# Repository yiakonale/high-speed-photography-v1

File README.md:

# High Speed Photography Unit V1

The problem with capturing high-speed photos boils down to how fast the camera can sample the subject. In nearly all cameras digital or analog, it comes down to the shutter speed. The shutter speed dictates how long the sensor (analog or digital) is exposed for, and therefore the "speed" of the photo. Regular digital cameras can expose a photo to 1/250 or 1/500 of a second. The fastest camera I own is an SLR with a mechanical shutter that can do 1/4000 of a second, which means that the film is exposed for 250us. One can optimize for faster and faster shutter speeds but the next bottleneck becomes the sensor itself. The less time you expose for, the less light the sensor can absorb. You can optimize for maximum light sensitivity but that's when the cost also skyrockets.

One workaround to this, is instead of relying on an ultra-fast shutter for quick exposure, instead using an ultra-fast light source to expose the event. The camera is set up to take a long exposure with large aperture and in complete darkness. When the event is you wish to capture takes place, the light source is triggered and exposes the scene for a very short instant. This works in the reverse way as before, as we now control the light source and leave the shutter wide open. The advantage to doing this is that you can use any regular camera, so long as you can take a long exposure. In order to know when you should pulse the light source, you need a way of knowing when your event is taking place, and very quickly triggerring a flash of light. A good video explanation of this concept can be found [here](https://www.youtube.com/watch?v=P-4pbFcERnk).

A reliable way of quickly detecting when to trigger the light source is to use acoustic waves or sound. The only downside to this is that the event itself has to produce some kind of noise or sound at the instant we wish to capture. Fortunately, there are many such events that produce a noise such as a balloon pop, champagne popping, things smashing into other objects, etc.
To capture a clean photo an event, we need to produce a pulse of light to expose the scene. The difficulty is creating a flash which is both bright enough and short enough to not cause blurring. Fortunately modern camera flashes are more than capable of producing sharp, bright flashes in an instant. Such flashtubes commonly contain high-pressure xenon gas in a sealed glass tube that get ionized by a pulse of high-voltage, momentarily allowing a large amount of current to flow through the tube which creates the bright flash. The gas can be ionized by wrapping a coil of wire around the glass tube and pulsing high-voltage. The high-voltage can capacitively couple through the gas and create plasma. The ends of the flashtube are also connected to a high voltage DC source, usually a capacitor. When the plasma is initially created, the strong electric field inside the tube accelerates the charged particles, creating a cascading avalanche effect until all or most of the gas is ionized. Once a low impedance connection is established through the plasma, the capacitor can rapidly discharge through the glass, heating it in the process and creating a bright flash of light.

###### Source: https://www.ecplaza.net/products/xenon-flash-lamp_3895024

To make this work, we need 3 main components. The first is a sound detector that can sense changes in air pressure that will generate the signal for the light to flash. We want this to be sensitive enough to detect sounds from a few meters distance, but not too sensitive to avoid accidental misfires. Something adjustable would be ideal. The second is a trigger circuit that can ionize the flashtube when the signal is sent by the detector. A trigger transformer in combination with an electronic switch is often used to create the HV pulse. I salvaged the trigger transformer, high-voltage capacitor as well as the flashtube from an old digital camera, though I've also seen them being used in wall mounted fire alarm sirens like [this one](https://www.shutterstock.com/video/clip-10242920-fire-alarm-emergency-flashing-light) as these use a similar circuit. You can actually just make out the coil of wire around the flashlamp in the center. You can also buy the entire circuit on [Ebay](https://www.ebay.ca/itm/125804677365). Lastly, we'll need a step-up converter to charge our capacitor, usually in the range of 300-400V and a few tens of microfarads.

###### (Left) Digital camera opened with high-voltage module and flashlamp visible in the middle (Right) Holding the high-voltage module from its HV capacitor. Trigger transformer visible in the middle of the PCB (orange). Flashtube visible just behind with its 3 wires: +, -, HV trigger.

I decided to design 3 PCBs, one for each subcircuit and then connect them together somehow. Not a lot of thought went into this phase as will be evident later on. The trigger circuit is really simple. It consists of an electronic switch, in this case a thyristor that can safely control the high-voltage pulse. I've also seen this being done with IGBTs but thyristors are easier to find for this application. To create the high voltage pulse, we need a high turn-ratio transformer, as well as a series capacitor. This small capacitor slowly charges through a resistor and rapidly discharges through the primary of the transformer, creating a high voltage spark on the output, similar to an electrostatic discharge. This is enough to break down the gas inside the tube.

TODO:
- trigger cct construction
- boost cct construction
- tuning capacitance

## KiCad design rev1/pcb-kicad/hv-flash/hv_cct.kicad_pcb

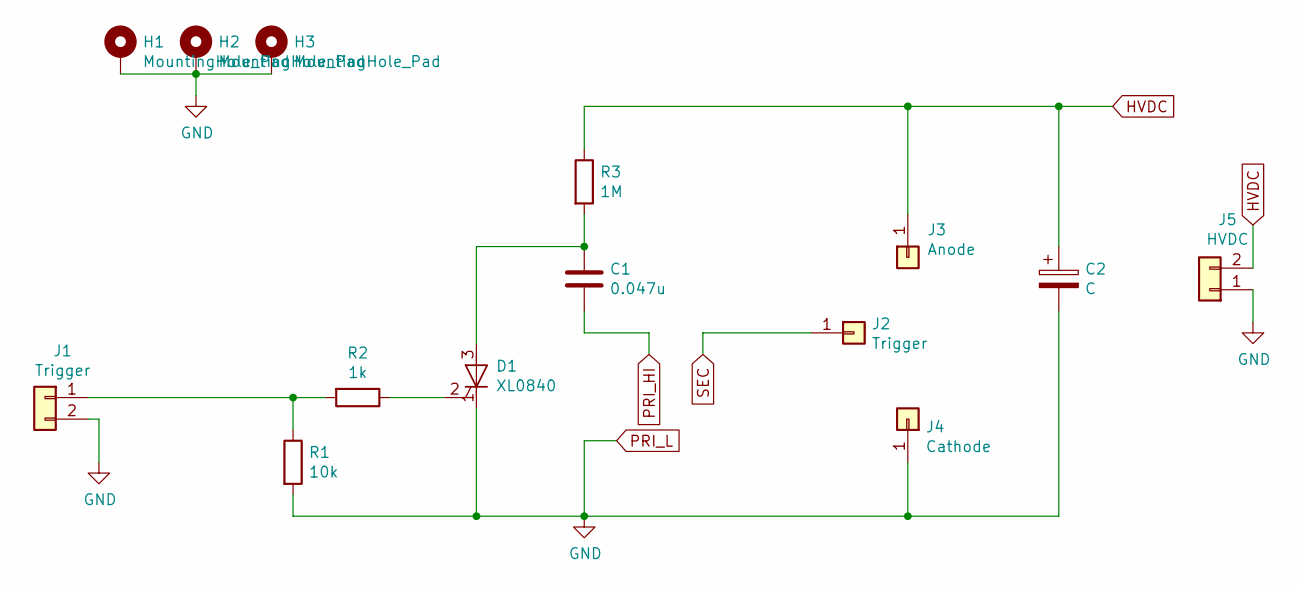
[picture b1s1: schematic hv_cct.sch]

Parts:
C1: 0.047u; C_Rect_L10.3mm_W5.0mm_P7.50mm_MKS4
C2: C; CP_Radial_D7.5mm_P2.50mm
D1: XL0840; TO-92_Inline_Wide
H1, H2, H3: MountingHole_Pad; MountingHole_3.2mm_M3_Pad
J1: Trigger; PinHeader_1x02_P2.54mm_Vertical
J2: Trigger; PinHeader_1x01_P2.54mm_Vertical
J3: Anode; PinHeader_1x01_P2.54mm_Vertical
J4: Cathode; PinHeader_1x01_P2.54mm_Vertical
J5: HVDC; PinHeader_1x02_P2.54mm_Vertical
R1: 10k; R_Axial_DIN0207_L6.3mm_D2.5mm_P7.62mm_Horizontal
R2: 1k; R_Axial_DIN0207_L6.3mm_D2.5mm_P7.62mm_Horizontal
R3: 1M; R_Axial_DIN0207_L6.3mm_D2.5mm_P7.62mm_Horizontal

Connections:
HVDC: C2.1, J3.1, J5.2, R3.1
unnamed: C1.1, D1.3 (A), R3.2
unnamed: D1.2 (G), R2.1
unnamed: J1.1, R1.1, R2.2
PRI_HI: C1.2
PRI_L: C2.2, D1.1 (K), H1.1, H2.1, H3.1, J1.2, J4.1, J5.1, R1.2
SEC: J2.1

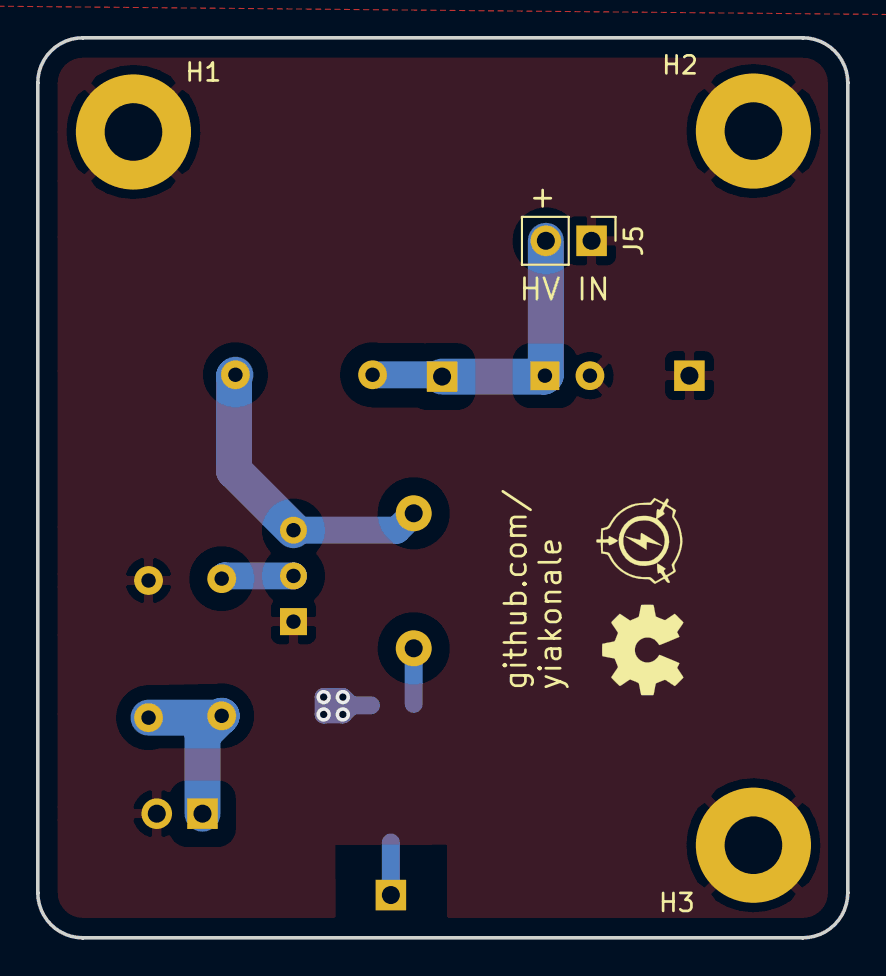
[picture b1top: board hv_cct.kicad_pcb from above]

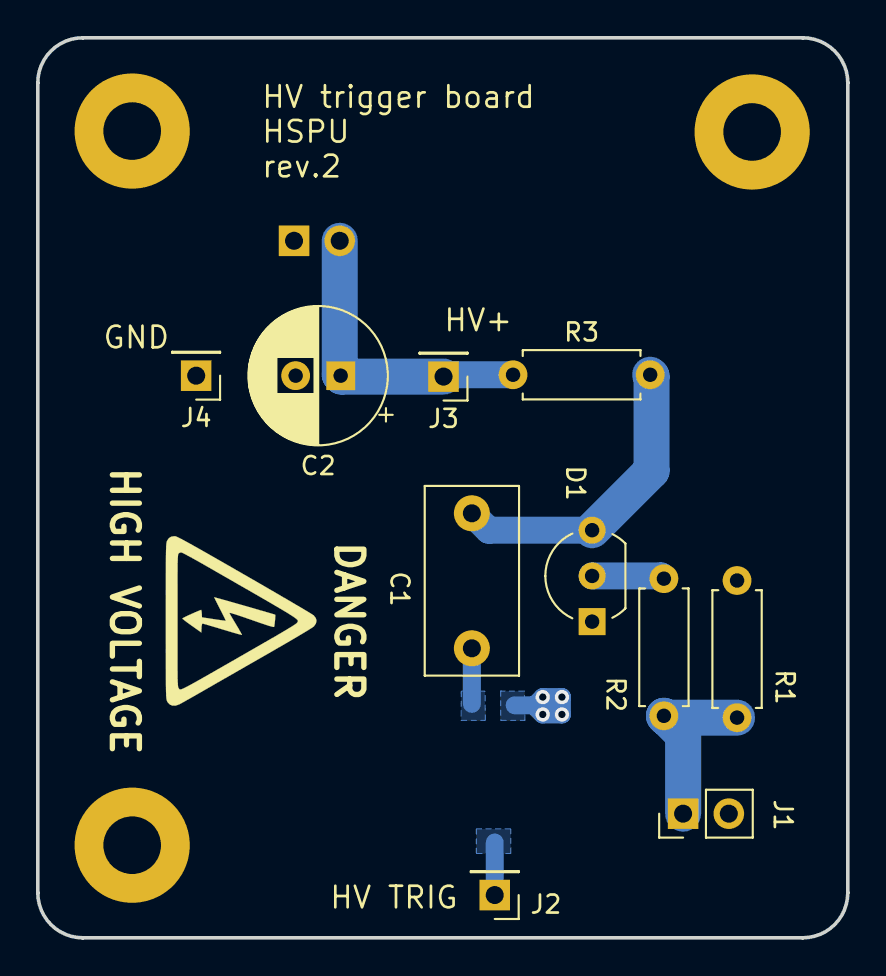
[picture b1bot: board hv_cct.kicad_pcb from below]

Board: 2 copper layers, 45.0 x 50.0 mm, 14 parts (10 on the bottom side), 5 nets.

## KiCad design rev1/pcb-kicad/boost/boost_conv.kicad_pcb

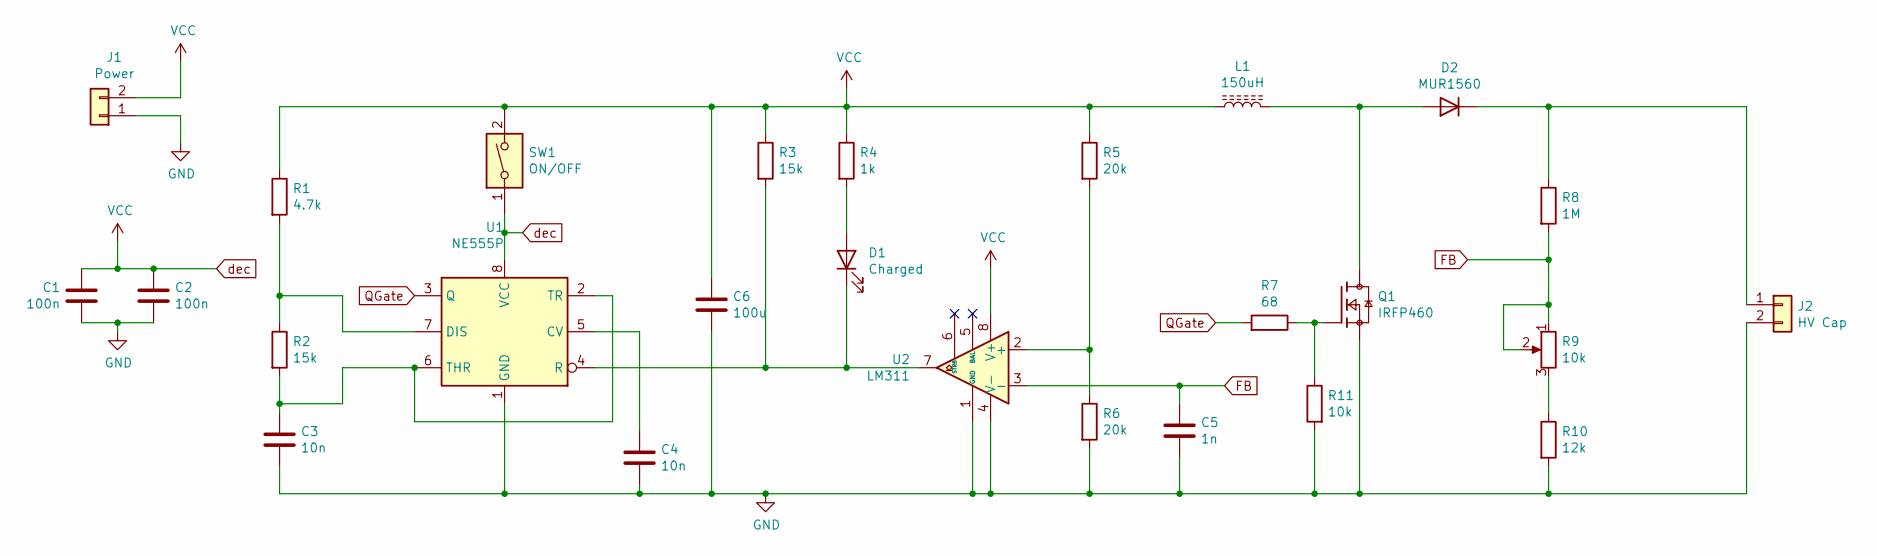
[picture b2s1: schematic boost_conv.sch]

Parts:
C1, C2: 100n; C_Disc_D5.0mm_W2.5mm_P5.00mm
C3, C4: 10n; C_Disc_D5.0mm_W2.5mm_P5.00mm
C5: 1n; C_Disc_D5.0mm_W2.5mm_P5.00mm
C6: 100u; CP_Radial_D8.0mm_P2.50mm
D1: Charged; LED_D5.0mm
D2: MUR1560; TO-220-2_Vertical
J1: Power; PinHeader_1x02_P2.54mm_Vertical
J2: HV Cap; PinHeader_1x02_P2.54mm_Vertical
L1: 150uH; L_Toroid_Vertical_L26.7mm_W14.0mm_P10.16mm_Pulse_D
Q1: IRFP460; TO-247-3_Vertical; PARTREV A
R1: 4.7k; R_Axial_DIN0207_L6.3mm_D2.5mm_P7.62mm_Horizontal
R2, R3: 15k; R_Axial_DIN0207_L6.3mm_D2.5mm_P7.62mm_Horizontal
R4: 1k; R_Axial_DIN0207_L6.3mm_D2.5mm_P7.62mm_Horizontal
R5, R6: 20k; R_Axial_DIN0207_L6.3mm_D2.5mm_P7.62mm_Horizontal
R7: 68; R_Axial_DIN0207_L6.3mm_D2.5mm_P7.62mm_Horizontal
R8: 1M; R_Axial_DIN0207_L6.3mm_D2.5mm_P7.62mm_Horizontal
R9: 10k; Potentiometer_Bourns_3296W_Vertical
R10: 12k; R_Axial_DIN0207_L6.3mm_D2.5mm_P7.62mm_Horizontal
R11: 10k; R_Axial_DIN0207_L6.3mm_D2.5mm_P7.62mm_Horizontal
SW1: ON/OFF; PinHeader_1x02_P2.54mm_Vertical
U1: NE555P; DIP-8_W7.62mm
U2: LM311; DIP-8_W7.62mm

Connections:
FB: C5.1, R8.2, R9.1, R9.2, U2.3 (-)
GND: C1.2, C2.2, C3.2, C4.2, C5.2, C6.2, J1.1, J2.2, Q1.3, R6.2, R10.2, R11.2, U1.1 (GND), U2.1 (GND), U2.4 (V-)
unnamed: C3.1, R2.2, U1.2 (TR), U1.6 (THR)
unnamed: C4.1, U1.5 (CV)
unnamed: D1.1 (K), R3.2, U1.4 (R), U2.7
unnamed: D1.2 (A), R4.2
unnamed: D2.1 (K), J2.1, R8.1
unnamed: D2.2 (A), L1.1, Q1.2
unnamed: Q1.1, R7.1, R11.1
unnamed: R1.2, R2.1, U1.7 (DIS)
unnamed: R5.2, R6.1, U2.2 (+)
unnamed: R9.3, R10.1
QGate: R7.2, U1.3 (Q)
dec: C1.1, C2.1, C6.1, J1.2, L1.2, R1.1, R3.1, R4.1, R5.1, SW1.1, SW1.2, U1.8 (VCC), U2.8 (V+)

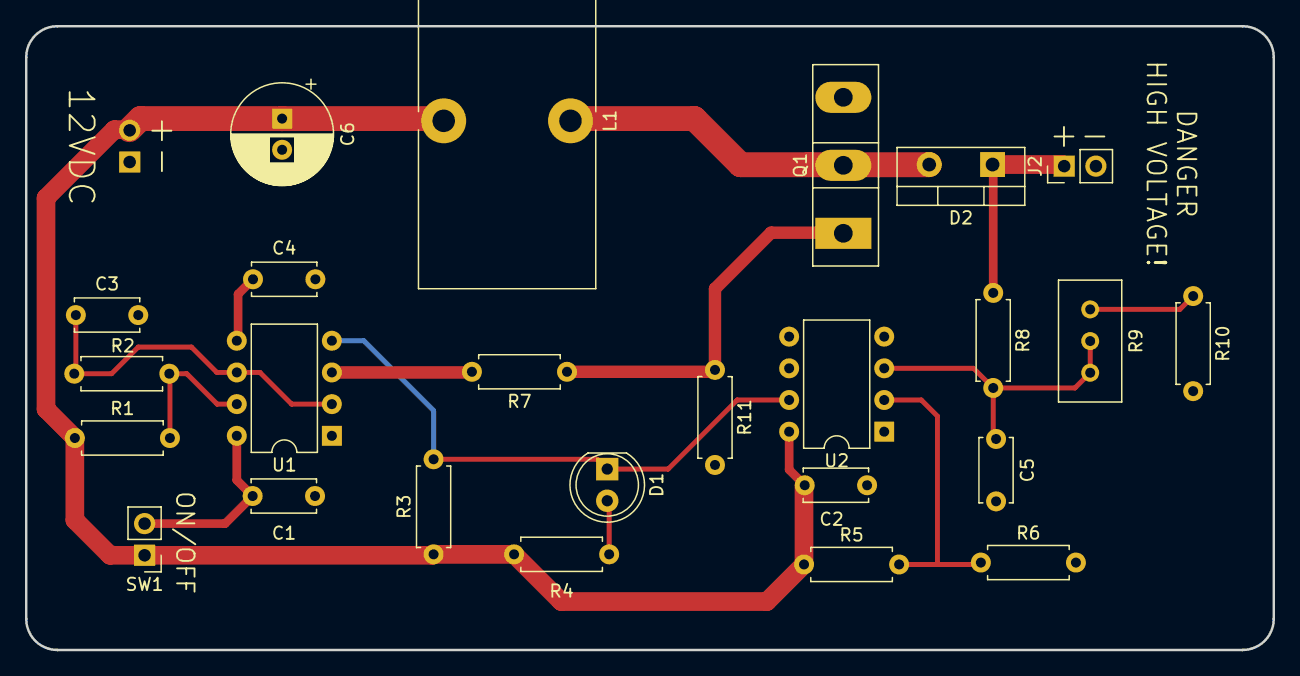
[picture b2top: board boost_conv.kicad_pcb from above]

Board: 2 copper layers, 100.0 x 50.0 mm, 26 parts (1 on the bottom side), 14 nets.

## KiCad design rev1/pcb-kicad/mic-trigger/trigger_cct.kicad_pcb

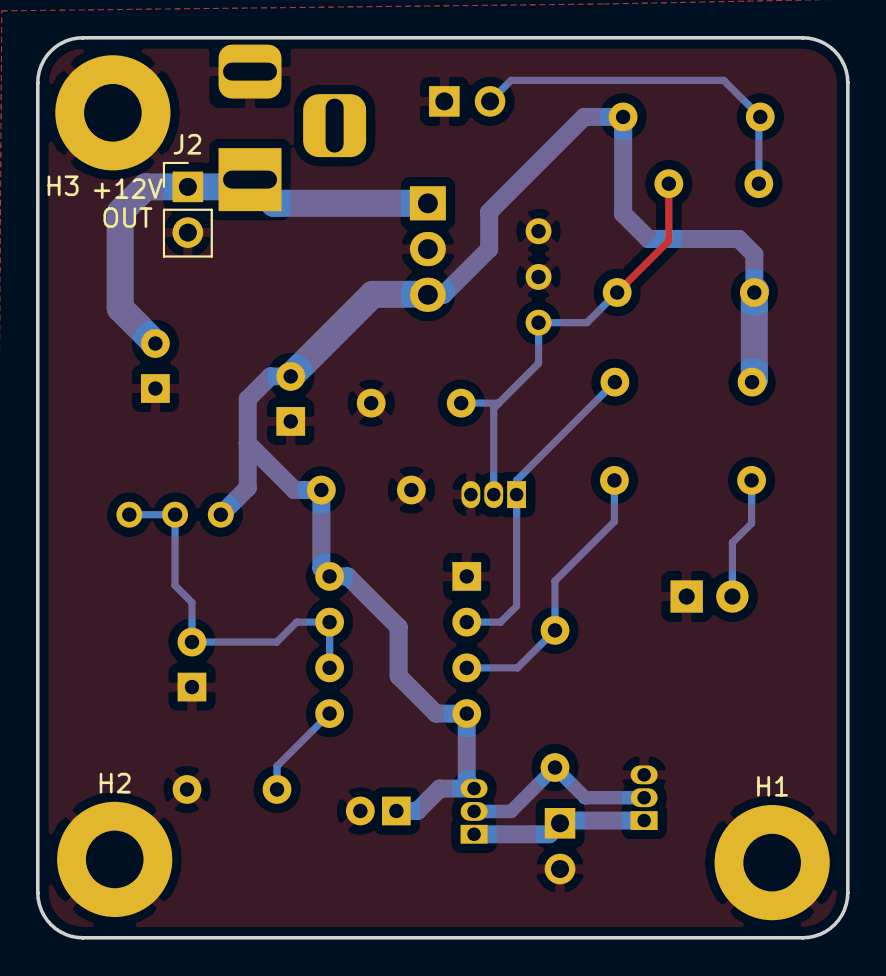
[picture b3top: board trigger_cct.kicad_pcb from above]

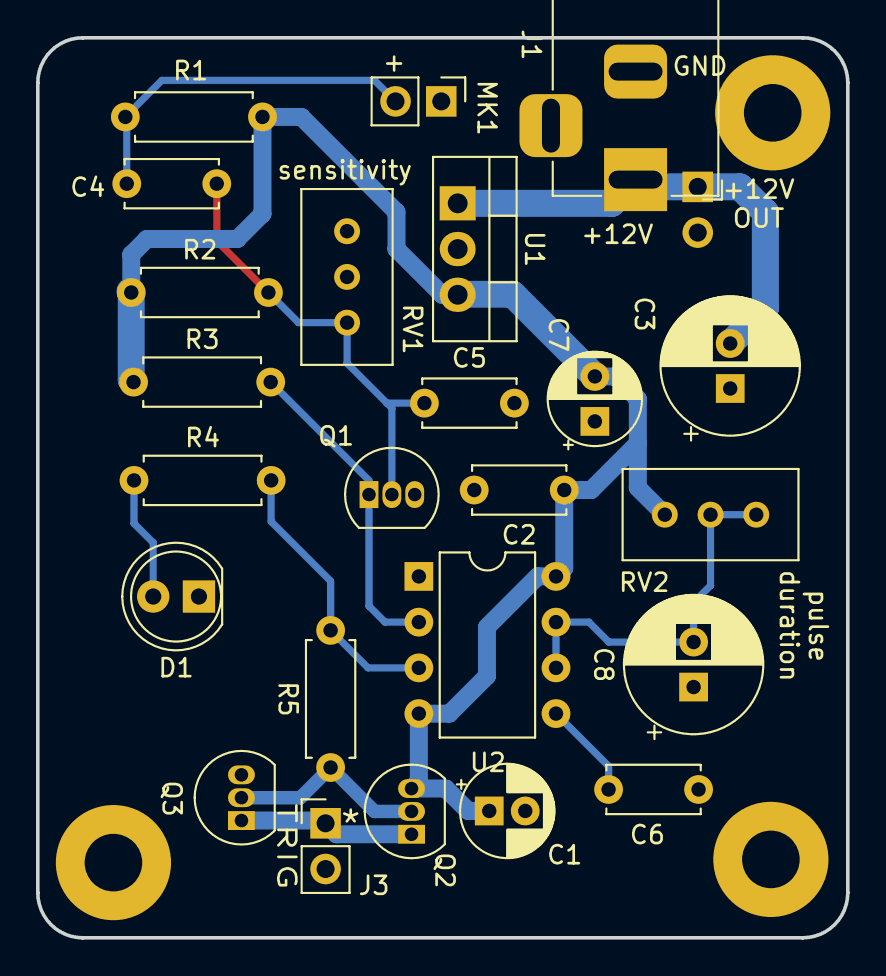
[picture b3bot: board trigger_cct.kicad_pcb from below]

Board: 2 copper layers, 45.0 x 50.0 mm, 28 parts (24 on the bottom side), 12 nets.

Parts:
C1: 1u; CP_Radial_D5.0mm_P2.00mm
C2: 100n; C_Disc_D5.0mm_W2.5mm_P5.00mm
C3: 10u; CP_Radial_D7.5mm_P2.50mm
C4: 220n; C_Disc_D5.0mm_W2.5mm_P5.00mm
C5, C6: 10n; C_Disc_D5.0mm_W2.5mm_P5.00mm
C7: 1u; CP_Radial_D5.0mm_P2.50mm
C8: 100u; CP_Radial_D7.5mm_P2.50mm
D1: LED; LED_D5.0mm
H1, H2, H3: MountingHole_Pad; MountingHole_3.2mm_M3_Pad
J1: 12V_IN; BarrelJack_Horizontal
J2: 12V_OUT; PinHeader_1x02_P2.54mm_Vertical
J3: Trigger; PinHeader_1x02_P2.54mm_Vertical
MK1: Mic; PinHeader_1x02_P2.54mm_Vertical
Q1: BC550; TO-92_Inline
Q2: 2N3904; TO-92_Inline
Q3: 2N3906; TO-92_Inline
R1: 2.2k; R_Axial_DIN0207_L6.3mm_D2.5mm_P7.62mm_Horizontal
R2: 470k; R_Axial_DIN0207_L6.3mm_D2.5mm_P7.62mm_Horizontal
R3: 20k; R_Axial_DIN0207_L6.3mm_D2.5mm_P7.62mm_Horizontal
R4: 1k; R_Axial_DIN0207_L6.3mm_D2.5mm_P7.62mm_Horizontal
R5: 100; R_Axial_DIN0207_L6.3mm_D2.5mm_P7.62mm_Horizontal
RV1, RV2: 100k; Potentiometer_Bourns_3296W_Vertical
U1: L7805; TO-220-3_Vertical
U2: NE555P; DIP-8_W7.62mm

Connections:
+5V: C1.1, C2.1, C7.2, Q2.3, R1.1, R2.1, R3.1, RV2.1, U1.3, U2.4, U2.8
+12V: C3.2, J1.1, J2.1, U1.1
GND: C1.2, C2.2, C3.1, C5.2, C6.2, C7.1, C8.1, D1.1, H1.1, H2.1, H3.1, J1.2, J2.2, J3.2, MK1.1, Q1.3, Q3.3, RV1.2, RV1.3, U1.2, U2.1
unnamed: C4.1, C5.1, Q1.2, R2.2, RV1.1
unnamed: C4.2, MK1.2, R1.2
unnamed: C6.1, U2.5
unnamed: C8.2, RV2.2, RV2.3, U2.6, U2.7
unnamed: D1.2, R4.1
unnamed: J3.1, Q2.1, Q3.1
unnamed: Q1.1, R3.2, U2.2
unnamed: Q2.2, Q3.2, R5.1
unnamed: R4.2, R5.2, U2.3

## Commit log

2023-10-06 init
2024-06-21 rev 1 pcb project + ltspice boost sim
2025-10-30 test
2026-02-12 docs
2026-02-12 photos
